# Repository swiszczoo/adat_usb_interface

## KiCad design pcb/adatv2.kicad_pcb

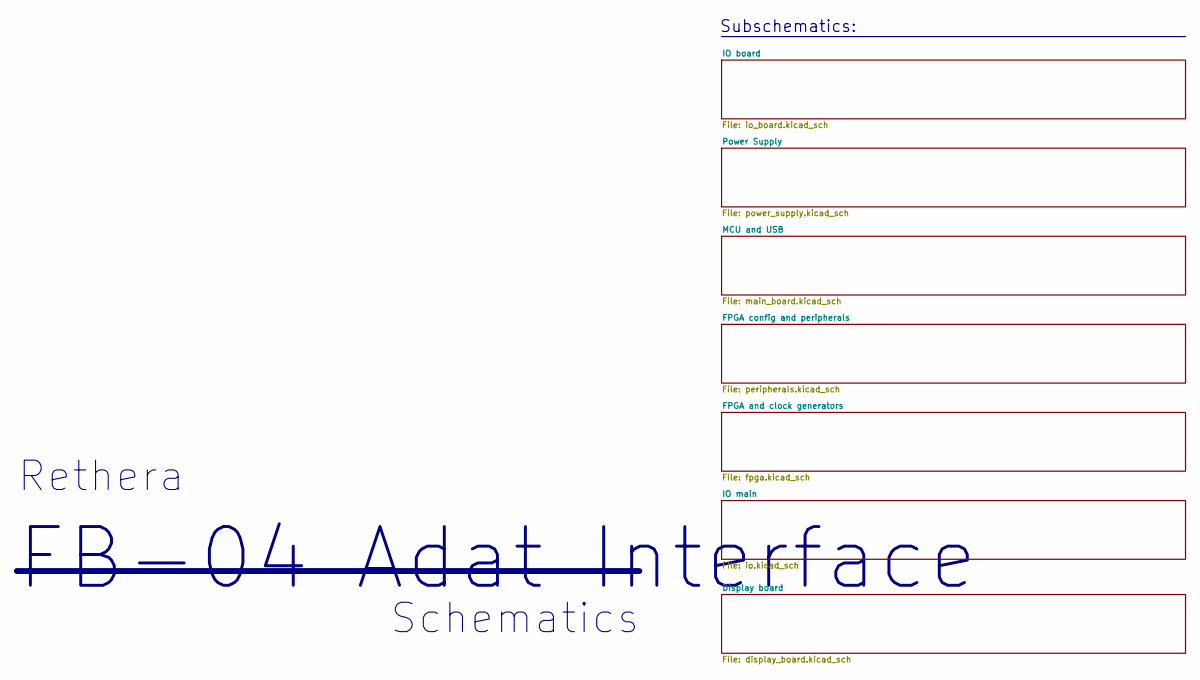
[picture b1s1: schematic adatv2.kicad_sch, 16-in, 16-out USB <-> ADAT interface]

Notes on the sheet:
Subschematics:
FB-04 Adat Interface
Schematics
Rethera

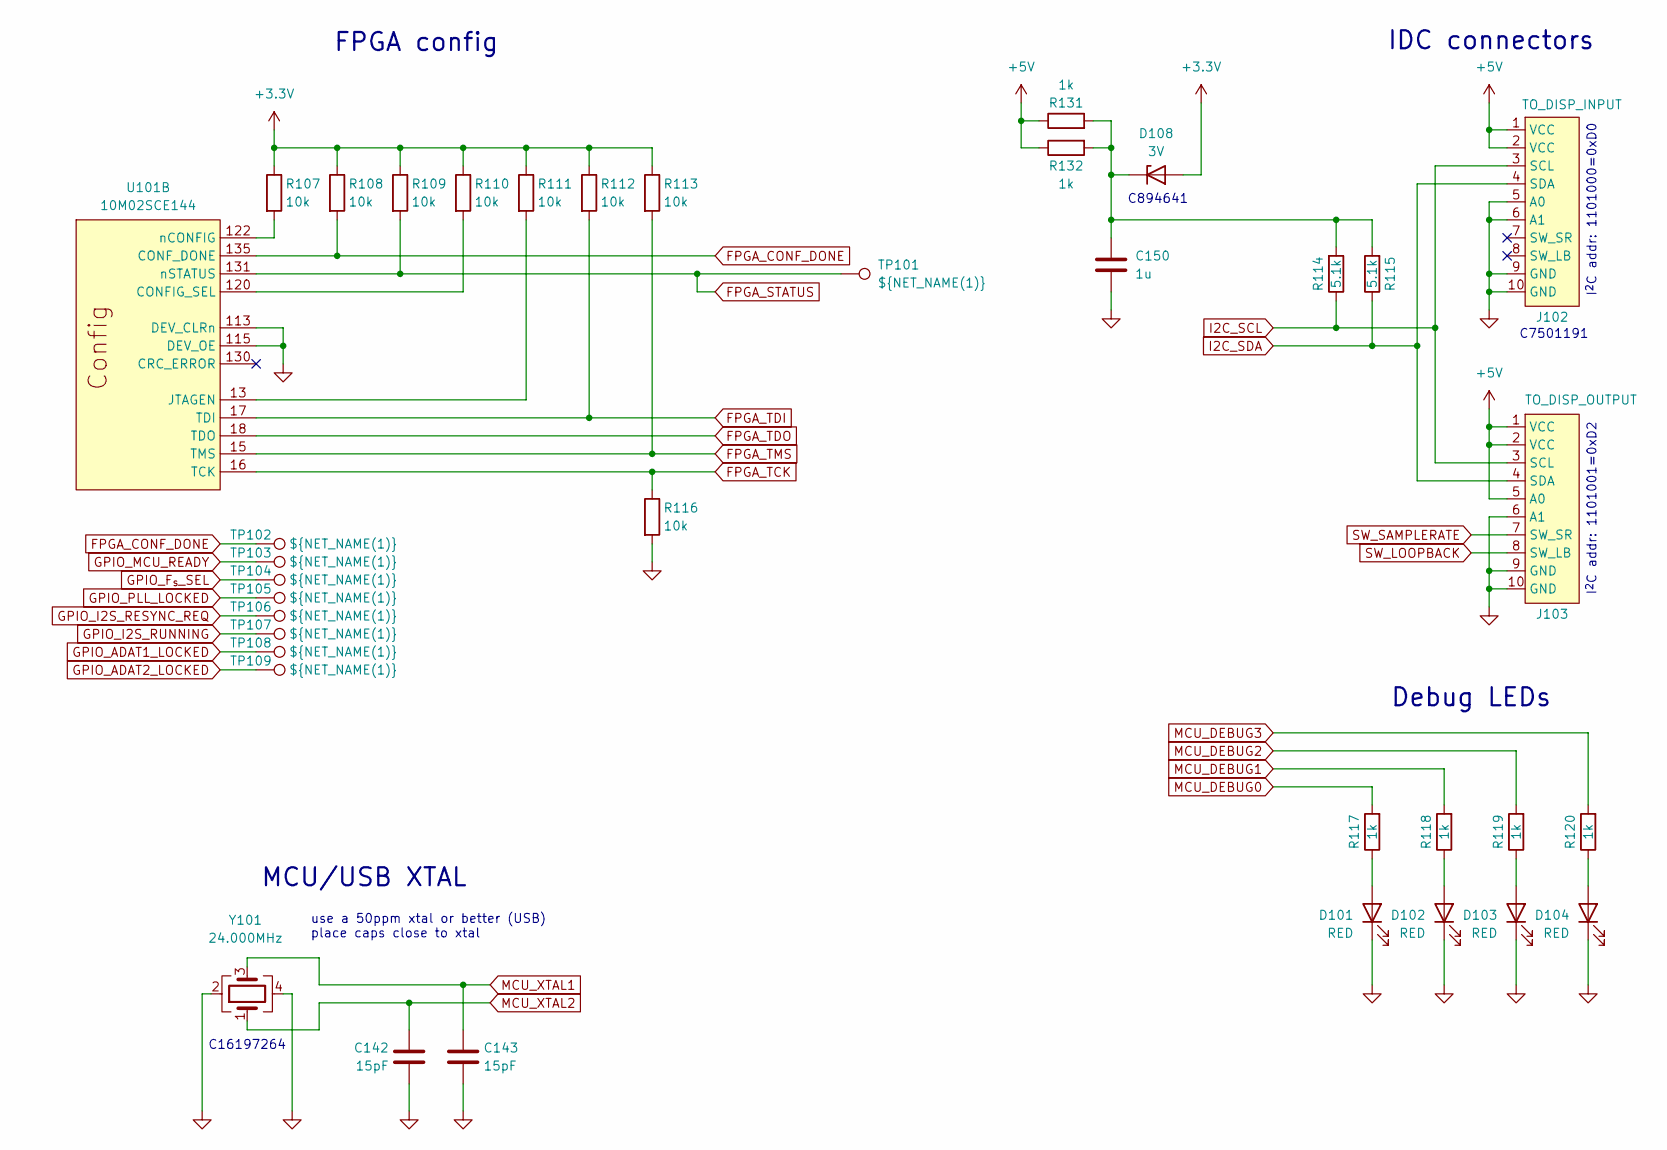
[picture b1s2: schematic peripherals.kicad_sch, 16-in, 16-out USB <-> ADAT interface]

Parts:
C142, C143: 15pF; C_0805_2012Metric_Pad1.18x1.45mm_HandSolder
C150: 1u; C_0805_2012Metric_Pad1.18x1.45mm_HandSolder
D101, D102, D103, D104: RED; LED_0805_2012Metric_Pad1.15x1.40mm_HandSolder
D108: 3V; D_SOD-123
J102: TO_DISP_INPUT; IDC-Header_2x05_P2.54mm_Vertical
J103: TO_DISP_OUTPUT; IDC-Header_2x05_P2.54mm_Vertical
R107, R108, R109, R110, R111, R112, R113, R116: 10k; R_0805_2012Metric_Pad1.20x1.40mm_HandSolder
R114, R115: 5.1k; R_0805_2012Metric_Pad1.20x1.40mm_HandSolder
R117, R118, R119, R120, R131, R132: 1k; R_0805_2012Metric_Pad1.20x1.40mm_HandSolder
TP101, TP102, TP103, TP104, TP105, TP106, TP107, TP108, TP109: ${NET_NAME(1)}; TestPoint_Pad_D2.5mm
U101: 10M02SCE144; EQFP-144-1EP_20x20mm_P0.5mm_EP4x4mm
Y101: 24.000MHz; Oscillator_SMD_Abracon_ASE-4Pin_3.2x2.5mm_HandSoldering

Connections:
+3.3V: D108.2 (A), R107.1, R108.1, R109.1, R110.1, R111.1, R112.1, R113.1; also elsewhere on the board
+5V: J102.1 (VCC), J102.2 (VCC), J103.1 (VCC), J103.2 (VCC), J103.5 (A0), R131.1, R132.1; also elsewhere on the board
FPGA_CONF_DONE: R108.2, TP102.1, U101.135 (CONF_DONE); also elsewhere on the board
FPGA_STATUS: R109.2, TP101.1, U101.131 (nSTATUS); also elsewhere on the board
FPGA_TCK: R116.1, U101.16 (TCK); also elsewhere on the board
FPGA_TDI: R112.2, U101.17 (TDI); also elsewhere on the board
FPGA_TDO: U101.18 (TDO); also elsewhere on the board
FPGA_TMS: R113.2, U101.15 (TMS); also elsewhere on the board
GND: C142.2, C143.2, C150.2, D101.1 (K), D102.1 (K), D103.1 (K), D104.1 (K), J102.5 (A0), J102.6 (A1), J102.9 (GND), J102.10 (GND), J103.6 (A1), J103.9 (GND), J103.10 (GND), R116.2, U101.113 (DEV_CLRn), U101.115 (DEV_OE), Y101.2, Y101.4; also elsewhere on the board
GPIO_ADAT1_LOCKED: TP108.1; also elsewhere on the board
GPIO_ADAT2_LOCKED: TP109.1; also elsewhere on the board
GPIO_F_{s}_SEL: TP104.1; also elsewhere on the board
GPIO_I2S_RESYNC_REQ: TP106.1; also elsewhere on the board
GPIO_I2S_RUNNING: TP107.1; also elsewhere on the board
GPIO_MCU_READY: TP103.1; also elsewhere on the board
GPIO_PLL_LOCKED: TP105.1; also elsewhere on the board
I2C_SCL: J102.3 (SCL), J103.3 (SCL), R114.1; also elsewhere on the board
I2C_SDA: J102.4 (SDA), J103.4 (SDA), R115.1; also elsewhere on the board
MCU_DEBUG0: R117.2; also elsewhere on the board
MCU_DEBUG1: R118.2; also elsewhere on the board
MCU_DEBUG2: R119.2; also elsewhere on the board
MCU_DEBUG3: R120.2; also elsewhere on the board
MCU_XTAL1: C143.1, Y101.3; also elsewhere on the board
MCU_XTAL2: C142.1, Y101.1; also elsewhere on the board
unnamed: D101.2 (A), R117.1
unnamed: D102.2 (A), R118.1
unnamed: D103.2 (A), R119.1
unnamed: D104.2 (A), R120.1
unnamed: C150.1, D108.1 (K), R114.2, R115.2, R131.2, R132.2
unnamed: R110.2, U101.120 (CONFIG_SEL)
unnamed: R111.2, U101.13 (JTAGEN)
unnamed: R107.2, U101.122 (nCONFIG)
SW_LOOPBACK: J103.8 (SW_LB); also elsewhere on the board
SW_SAMPLERATE: J103.7 (SW_SR); also elsewhere on the board

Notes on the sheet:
C16197264
FPGA config
Debug LEDs
C894641
MCU/USB XTAL
I^{2}C addr: 1101000=0xD0
use a 50ppm xtal or better (USB) place caps close to xtal
I^{2}C addr: 1101001=0xD2
C7501191
IDC connectors

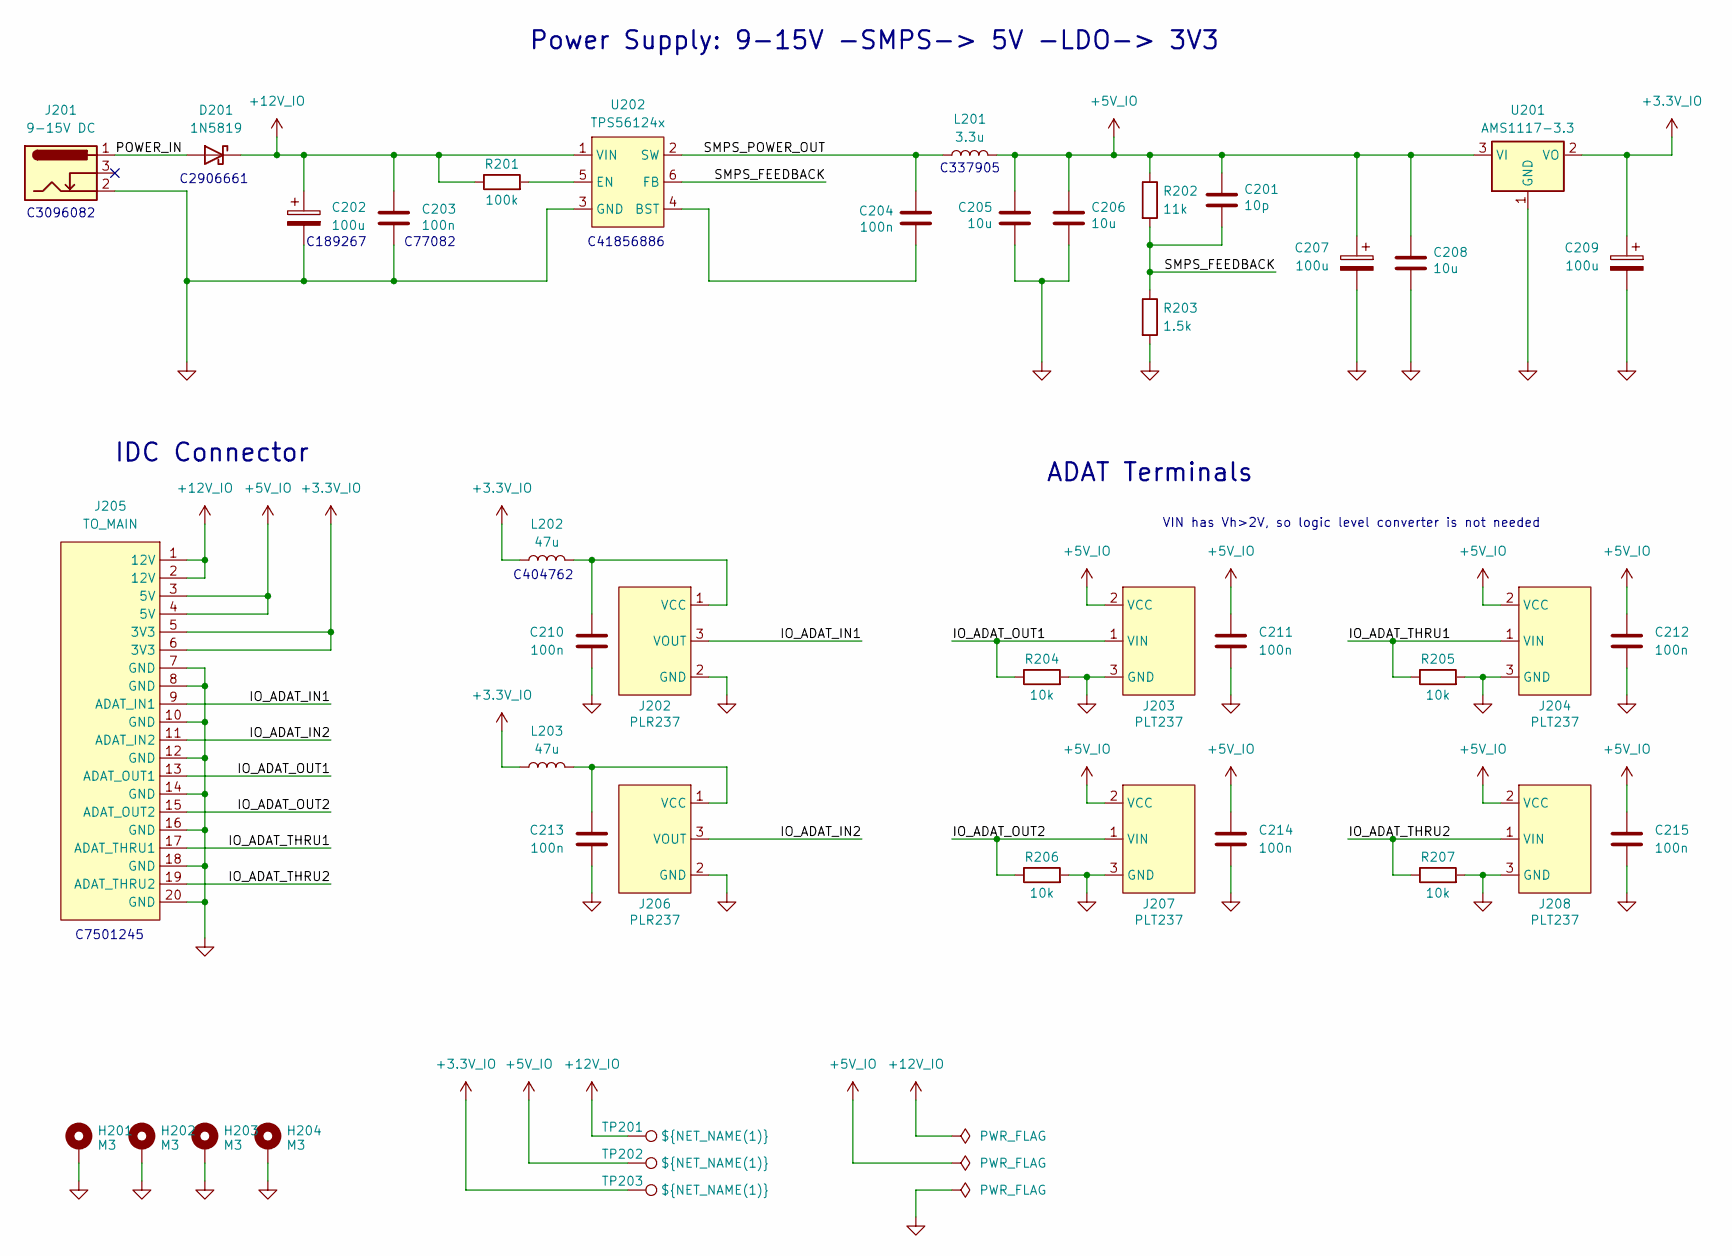
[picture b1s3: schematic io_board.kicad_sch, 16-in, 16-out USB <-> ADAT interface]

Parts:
C201: 10p; C_0805_2012Metric_Pad1.18x1.45mm_HandSolder
C202, C207, C209: 100u; C_Elec_6.3x5.4
C203, C204, C210, C211, C212, C213, C214, C215: 100n; C_0805_2012Metric_Pad1.18x1.45mm_HandSolder
C205, C206, C208: 10u; C_1206_3216Metric_Pad1.33x1.80mm_HandSolder
D201: 1N5819; D_DO-41_SOD81_P10.16mm_Horizontal
H201, H202, H203, H204: M3; MountingHole_3.2mm_M3_Pad
J201: 9-15V DC; CUI PJ-002A
J202, J206: PLR237; PLx237
J203, J204, J207, J208: PLT237; PLx237
J205: TO_MAIN; IDC-Header_2x10_P2.54mm_Vertical
L201: 3.3u; L_1210_3225Metric_Pad1.42x2.65mm_HandSolder
L202, L203: 47u; L_0805_2012Metric_Pad1.15x1.40mm_HandSolder
R201: 100k; R_0805_2012Metric_Pad1.20x1.40mm_HandSolder
R202: 11k; R_0805_2012Metric_Pad1.20x1.40mm_HandSolder
R203: 1.5k; R_0805_2012Metric_Pad1.20x1.40mm_HandSolder
R204, R205, R206, R207: 10k; R_0805_2012Metric_Pad1.20x1.40mm_HandSolder
TP201, TP202, TP203: ${NET_NAME(1)}; TestPoint_Pad_D2.5mm
U201: AMS1117-3.3; SOT-223-3_TabPin2
U202: TPS56124x; SOT-563

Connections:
+3.3V_IO: C209.1, J205.5 (3V3), J205.6 (3V3), L202.1, L203.1, TP203.1, U201.2 (VO)
+5V_IO: C201.1, C205.1, C206.1, C207.1, C208.1, C211.1, C212.1, C214.1, C215.1, J203.2 (VCC), J204.2 (VCC), J205.3 (5V), J205.4 (5V), J207.2 (VCC), J208.2 (VCC), L201.2, R202.1, TP202.1, U201.3 (VI)
+12V_IO: C202.1, C203.1, D201.1 (K), J205.1 (12V), J205.2 (12V), R201.1, TP201.1, U202.1 (VIN)
/IO board/IO_ADAT_IN1: J202.3 (VOUT), J205.9 (ADAT_IN1)
/IO board/IO_ADAT_IN2: J205.11 (ADAT_IN2), J206.3 (VOUT)
/IO board/IO_ADAT_OUT1: J203.1 (VIN), J205.13 (ADAT_OUT1), R204.1
/IO board/IO_ADAT_OUT2: J205.15 (ADAT_OUT2), J207.1 (VIN), R206.1
/IO board/IO_ADAT_THRU1: J204.1 (VIN), J205.17 (ADAT_THRU1), R205.1
/IO board/IO_ADAT_THRU2: J205.19 (ADAT_THRU2), J208.1 (VIN), R207.1
/IO board/POWER_IN: D201.2 (A), J201.1
/IO board/SMPS_FEEDBACK: C201.2, R202.2, R203.1, U202.6 (FB)
/IO board/SMPS_POWER_OUT: C204.1, L201.1, U202.2 (SW)
GND_IO: C202.2, C203.2, C205.2, C206.2, C207.2, C208.2, C209.2, C210.2, C211.2, C212.2, C213.2, C214.2, C215.2, H201.1, H202.1, H203.1, H204.1, J201.2, J202.2 (GND), J203.3 (GND), J204.3 (GND), J205.7 (GND), J205.8 (GND), J205.10 (GND), J205.12 (GND), J205.14 (GND), J205.16 (GND), J205.18 (GND), J205.20 (GND), J206.2 (GND), J207.3 (GND), J208.3 (GND), R203.2, R204.2, R205.2, R206.2, R207.2, U201.1 (GND), U202.3 (GND)
unnamed: C210.1, J202.1 (VCC), L202.2
unnamed: C213.1, J206.1 (VCC), L203.2
unnamed: C204.2, U202.4 (BST)
unnamed: R201.2, U202.5 (EN)

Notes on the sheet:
C41856886
C189267
C404762
C3096082
C337905
C2906661
C7501245
VIN has Vh>2V, so logic level converter is not needed
C77082
IDC Connector
Power Supply: 9-15V -SMPS-> 5V -LDO-> 3V3
ADAT Terminals

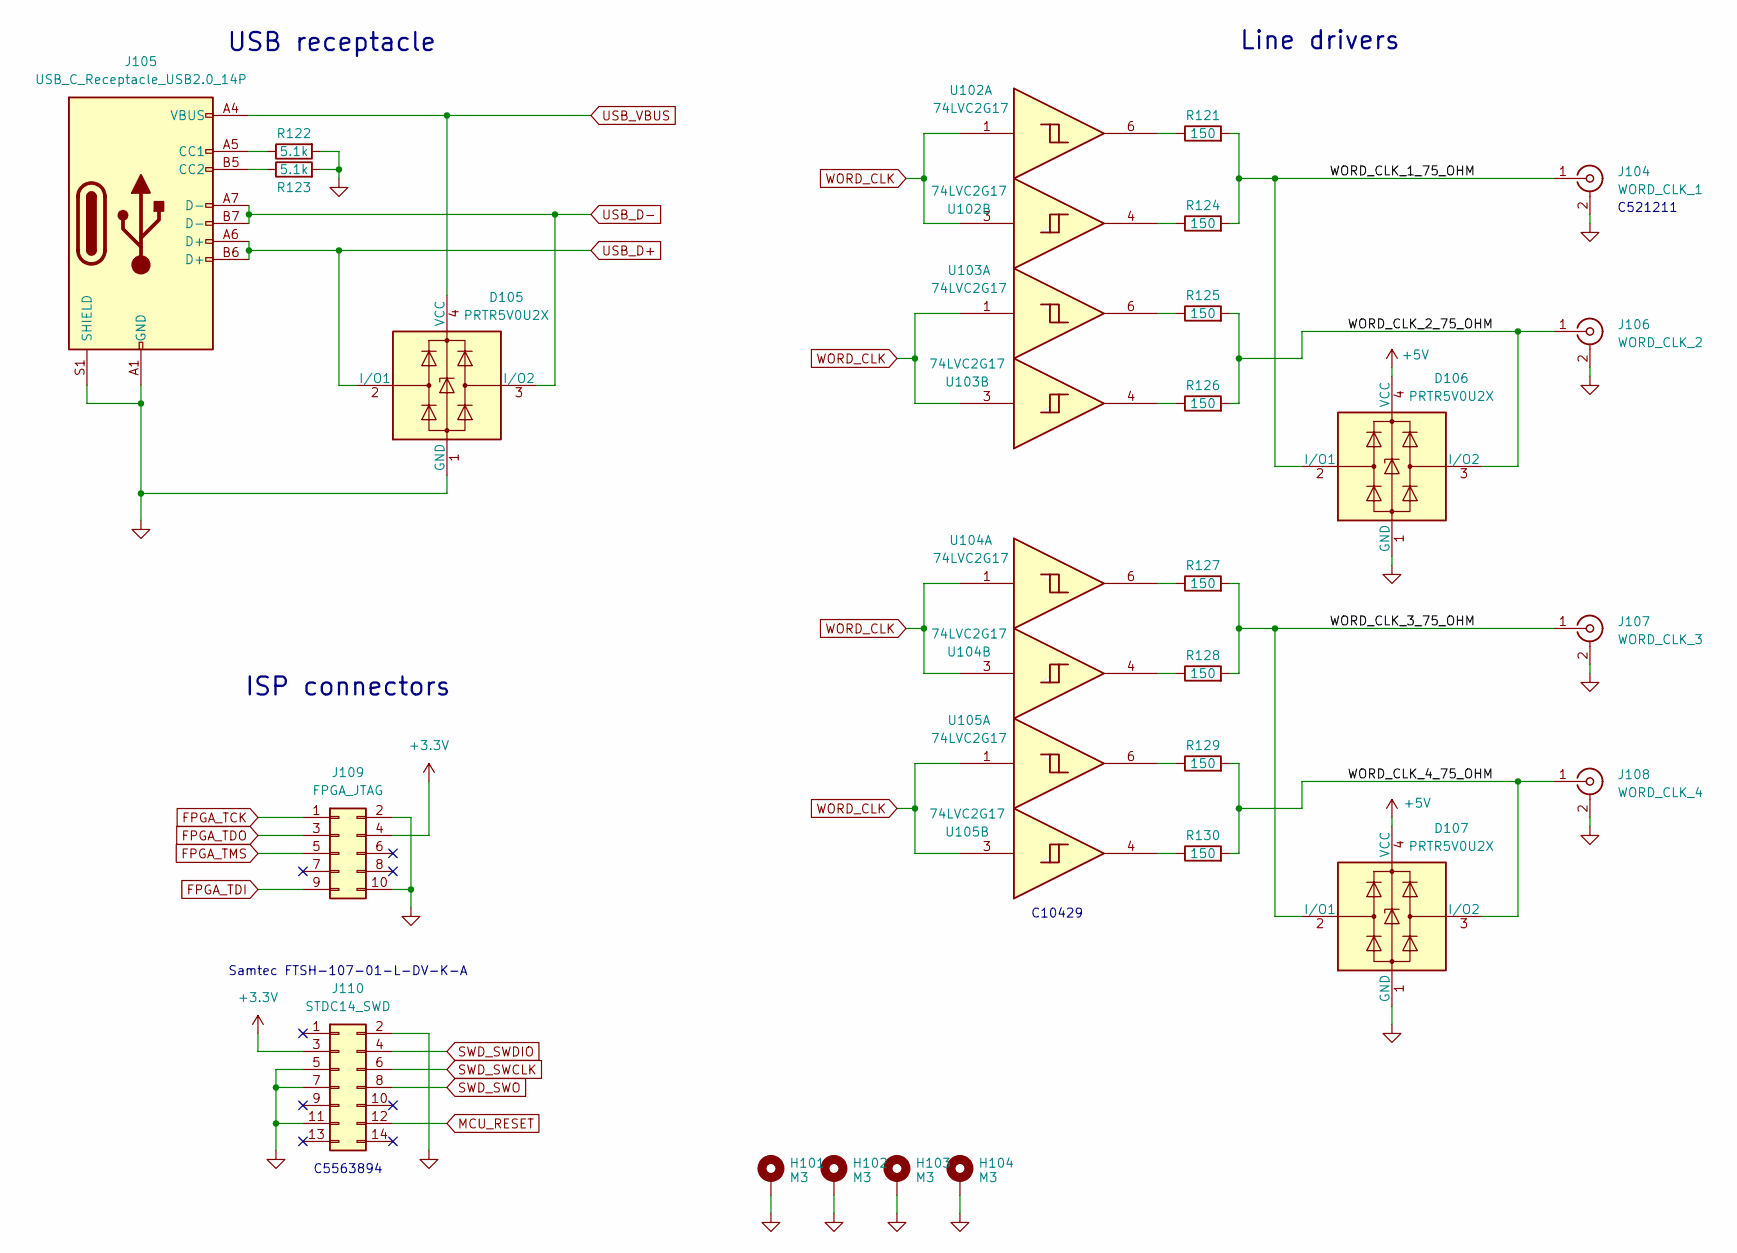
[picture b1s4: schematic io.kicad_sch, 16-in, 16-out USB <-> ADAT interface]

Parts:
D105, D106, D107: PRTR5V0U2X; SOT-143
H101, H102, H103, H104: M3; MountingHole_3.2mm_M3_Pad
J104: WORD_CLK_1; BNC_dosinconn_DOSIN-801-0051
J105: USB_C_Receptacle_USB2.0_14P; USB_C_Receptacle_GCT_USB4105-xx-A_16P_TopMnt_Horizontal
J106: WORD_CLK_2; BNC_dosinconn_DOSIN-801-0051
J107: WORD_CLK_3; BNC_dosinconn_DOSIN-801-0051
J108: WORD_CLK_4; BNC_dosinconn_DOSIN-801-0051
J109: FPGA_JTAG; IDC-Header_2x05_P2.54mm_Vertical
J110: STDC14_SWD; Samtec-FTSH-107-01-L-DV-K
R121, R124, R125, R126, R127, R128, R129, R130: 150; R_0805_2012Metric_Pad1.20x1.40mm_HandSolder
R122, R123: 5.1k; R_0805_2012Metric_Pad1.20x1.40mm_HandSolder
U102, U103, U104, U105: 74LVC2G17; SOT-23-6_Handsoldering

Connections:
+3.3V: J109.4, J110.3; also elsewhere on the board
+5V: D106.4 (VCC), D107.4 (VCC); also elsewhere on the board
/IO main/WORD_CLK_1_75_OHM: D106.2 (I/O1), J104.1 (In), R121.2, R124.2
/IO main/WORD_CLK_2_75_OHM: D106.3 (I/O2), J106.1 (In), R125.2, R126.2
/IO main/WORD_CLK_3_75_OHM: D107.2 (I/O1), J107.1 (In), R127.2, R128.2
/IO main/WORD_CLK_4_75_OHM: D107.3 (I/O2), J108.1 (In), R129.2, R130.2
FPGA_TCK: J109.1; also elsewhere on the board
FPGA_TDI: J109.9; also elsewhere on the board
FPGA_TDO: J109.3; also elsewhere on the board
FPGA_TMS: J109.5; also elsewhere on the board
GND: D105.1 (GND), D106.1 (GND), D107.1 (GND), H101.1, H102.1, H103.1, H104.1, J104.2 (Ext), J105.A1 (GND), J105.A12 (GND), J105.B1 (GND), J105.B12 (GND), J105.S1 (SHIELD), J106.2 (Ext), J107.2 (Ext), J108.2 (Ext), J109.2, J109.10, J110.2, J110.5, J110.7, J110.11, R122.2, R123.2; also elsewhere on the board
MCU_RESET: J110.12; also elsewhere on the board
unnamed: J105.A5 (CC1), R122.1
unnamed: J105.B5 (CC2), R123.1
unnamed: R121.1, U102.6
unnamed: R124.1, U102.4
unnamed: R125.1, U103.6
unnamed: R126.1, U103.4
unnamed: R127.1, U104.6
unnamed: R128.1, U104.4
unnamed: R129.1, U105.6
unnamed: R130.1, U105.4
SWD_SWCLK: J110.6; also elsewhere on the board
SWD_SWDIO: J110.4; also elsewhere on the board
SWD_SWO: J110.8; also elsewhere on the board
USB_D+: D105.2 (I/O1), J105.A6 (D+), J105.B6 (D+); also elsewhere on the board
USB_D-: D105.3 (I/O2), J105.A7 (D-), J105.B7 (D-); also elsewhere on the board
USB_VBUS: D105.4 (VCC), J105.A4 (VBUS), J105.A9 (VBUS), J105.B4 (VBUS), J105.B9 (VBUS); also elsewhere on the board
WORD_CLK: U102.1, U102.3, U103.1, U103.3, U104.1, U104.3, U105.1, U105.3; also elsewhere on the board

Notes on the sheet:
Line drivers
C10429
C5563894
Samtec FTSH-107-01-L-DV-K-A
USB receptacle
ISP connectors
C521211

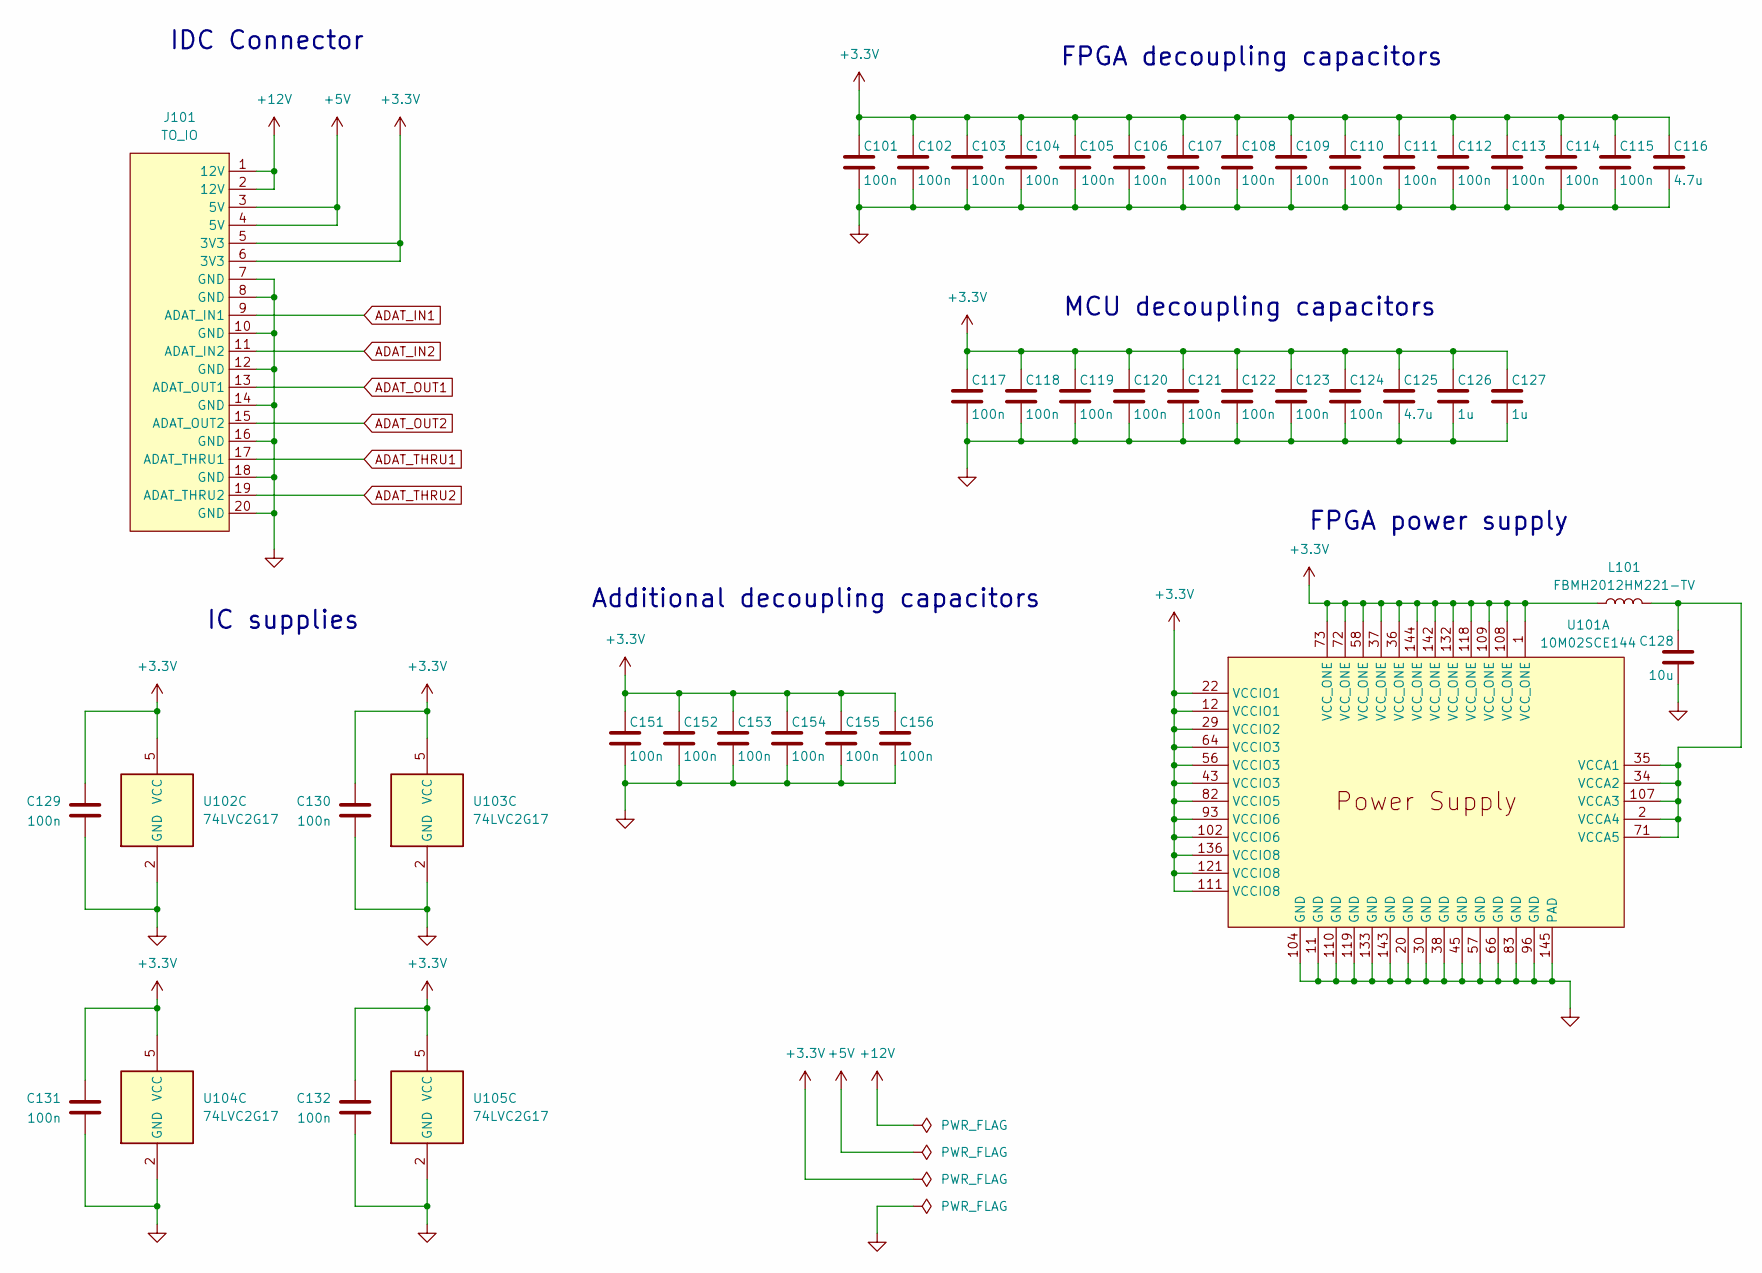
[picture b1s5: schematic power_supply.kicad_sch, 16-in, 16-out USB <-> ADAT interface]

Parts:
C101, C102, C103, C104, C105, C106, C107, C108, C109, C110, C111, C112, C113, C114, C115, C117, C118, C119, C120, C121, C122, C123, C124, C129, C130, C131, C132, C151, C152, C153, C154, C155, C156: 100n; C_0805_2012Metric_Pad1.18x1.45mm_HandSolder
C116, C125: 4.7u; C_0805_2012Metric_Pad1.18x1.45mm_HandSolder
C126, C127: 1u; C_0805_2012Metric_Pad1.18x1.45mm_HandSolder
C128: 10u; C_1206_3216Metric_Pad1.33x1.80mm_HandSolder
J101: TO_IO; IDC-Header_2x10_P2.54mm_Vertical
L101: FBMH2012HM221-TV; L_0805_2012Metric_Pad1.15x1.40mm_HandSolder
U101: 10M02SCE144; EQFP-144-1EP_20x20mm_P0.5mm_EP4x4mm
U102, U103, U104, U105: 74LVC2G17; SOT-23-6_Handsoldering

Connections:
+3.3V: C101.1, C102.1, C103.1, C104.1, C105.1, C106.1, C107.1, C108.1, C109.1, C110.1, C111.1, C112.1, C113.1, C114.1, C115.1, C116.1, C117.1, C118.1, C119.1, C120.1, C121.1, C122.1, C123.1, C124.1, C125.1, C126.1, C127.1, C129.1, C130.1, C131.1, C132.1, C151.1, C152.1, C153.1, C154.1, C155.1, C156.1, J101.5 (3V3), J101.6 (3V3), L101.1, U101.1 (VCC_ONE), U101.12 (VCCIO1), U101.22 (VCCIO1), U101.29 (VCCIO2), U101.36 (VCC_ONE), U101.37 (VCC_ONE), U101.43 (VCCIO3), U101.56 (VCCIO3), U101.58 (VCC_ONE), U101.64 (VCCIO3), U101.72 (VCC_ONE), U101.73 (VCC_ONE), U101.82 (VCCIO5), U101.93 (VCCIO6), U101.102 (VCCIO6), U101.108 (VCC_ONE), U101.109 (VCC_ONE), U101.111 (VCCIO8), U101.118 (VCC_ONE), U101.121 (VCCIO8), U101.132 (VCC_ONE), U101.136 (VCCIO8), U101.142 (VCC_ONE), U101.144 (VCC_ONE), U102.5 (VCC), U103.5 (VCC), U104.5 (VCC), U105.5 (VCC); also elsewhere on the board
+5V: J101.3 (5V), J101.4 (5V); also elsewhere on the board
+12V: J101.1 (12V), J101.2 (12V)
ADAT_IN1: J101.9 (ADAT_IN1); also elsewhere on the board
ADAT_IN2: J101.11 (ADAT_IN2); also elsewhere on the board
ADAT_OUT1: J101.13 (ADAT_OUT1); also elsewhere on the board
ADAT_OUT2: J101.15 (ADAT_OUT2); also elsewhere on the board
ADAT_THRU1: J101.17 (ADAT_THRU1); also elsewhere on the board
ADAT_THRU2: J101.19 (ADAT_THRU2); also elsewhere on the board
GND: C101.2, C102.2, C103.2, C104.2, C105.2, C106.2, C107.2, C108.2, C109.2, C110.2, C111.2, C112.2, C113.2, C114.2, C115.2, C116.2, C117.2, C118.2, C119.2, C120.2, C121.2, C122.2, C123.2, C124.2, C125.2, C126.2, C127.2, C128.2, C129.2, C130.2, C131.2, C132.2, C151.2, C152.2, C153.2, C154.2, C155.2, C156.2, J101.7 (GND), J101.8 (GND), J101.10 (GND), J101.12 (GND), J101.14 (GND), J101.16 (GND), J101.18 (GND), J101.20 (GND), U101.11 (GND), U101.20 (GND), U101.30 (GND), U101.38 (GND), U101.45 (GND), U101.57 (GND), U101.66 (GND), U101.83 (GND), U101.96 (GND), U101.104 (GND), U101.110 (GND), U101.119 (GND), U101.133 (GND), U101.143 (GND), U101.145 (PAD), U102.2 (GND), U103.2 (GND), U104.2 (GND), U105.2 (GND); also elsewhere on the board
unnamed: C128.1, L101.2, U101.2 (VCCA4), U101.34 (VCCA2), U101.35 (VCCA1), U101.71 (VCCA5), U101.107 (VCCA3)

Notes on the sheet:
IC supplies
IDC Connector
FPGA decoupling capacitors
FPGA power supply
Additional decoupling capacitors
MCU decoupling capacitors
